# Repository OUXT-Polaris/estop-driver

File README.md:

# estop-driver
PCB design files for a board that brings an emergency stop function with mechanical relays to the power supply of an autonomous mobile robot.

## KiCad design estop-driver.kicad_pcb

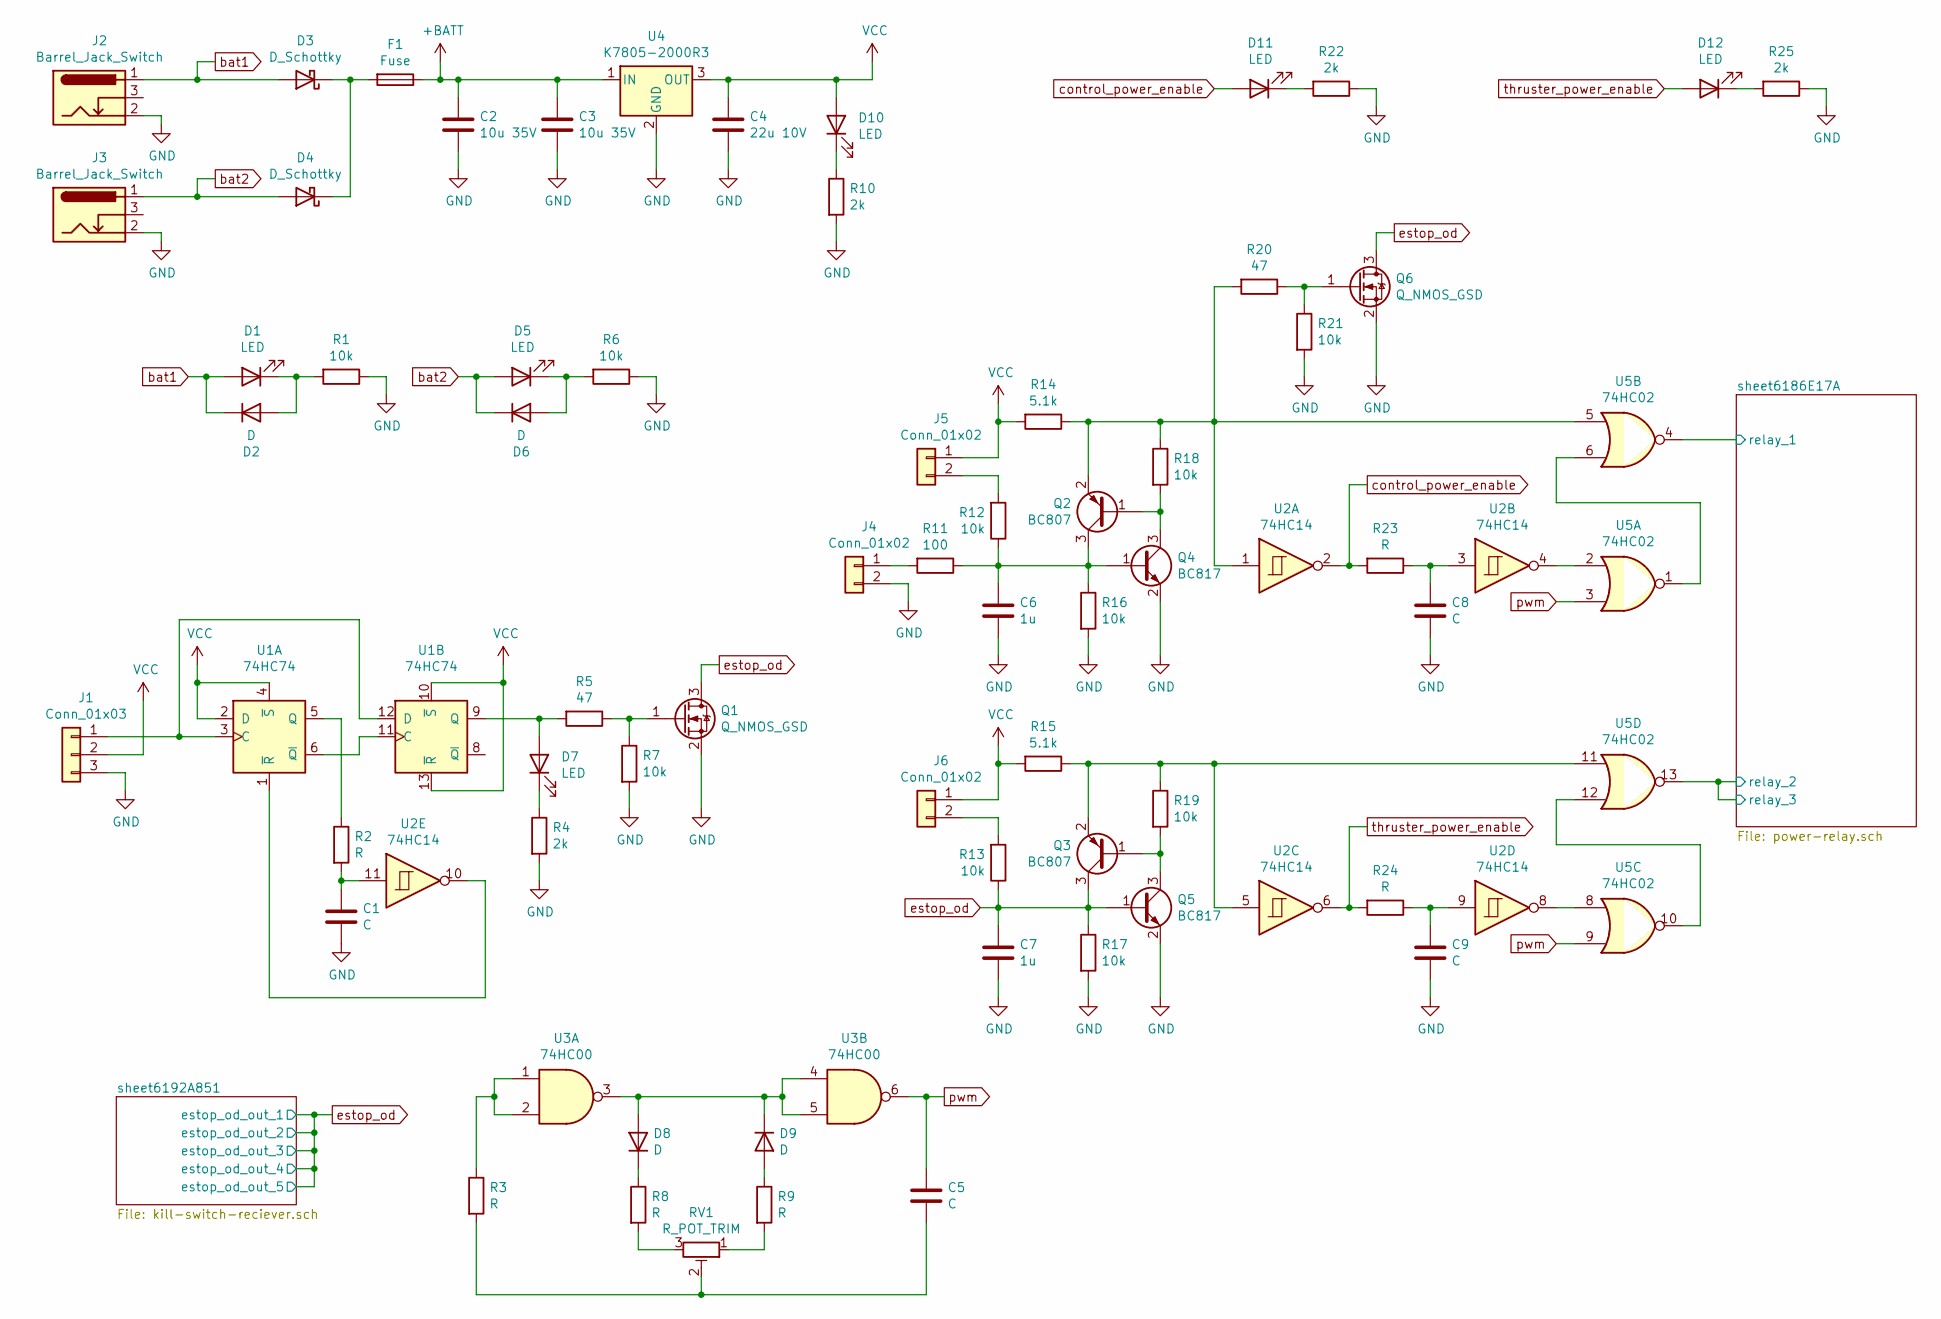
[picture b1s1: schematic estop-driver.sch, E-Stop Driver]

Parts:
C1, C5, C8, C9: C; C_0805_2012Metric_Pad1.15x1.40mm_HandSolder
C2, C3: 10u 35V; C_0805_2012Metric_Pad1.15x1.40mm_HandSolder
C4: 22u 10V; C_1206_3216Metric_Pad1.33x1.80mm_HandSolder
C6, C7: 1u; C_0805_2012Metric_Pad1.15x1.40mm_HandSolder
D1, D5, D7, D10, D11, D12: LED; LED_0603_1608Metric_Pad1.05x0.95mm_HandSolder
D2, D6, D8, D9: D; D_SOD-123
D3, D4: D_Schottky; D_SMC
F1: Fuse; RSPRO_1884617_plus_fuse
J1: Conn_01x03; PinHeader_1x03_P2.54mm_Vertical
J2, J3: Barrel_Jack_Switch; BarrelJack_Horizontal
J4, J5, J6: Conn_01x02; PinHeader_1x02_P2.54mm_Vertical
Q1, Q6: Q_NMOS_GSD; SOT-323_SC-70
Q2, Q3: BC807; SOT-23
Q4, Q5: BC817; SOT-23
R1, R6, R7, R12, R13, R16, R17, R18, R19, R21: 10k; R_0603_1608Metric_Pad0.98x0.95mm_HandSolder
R2, R3, R8, R9, R23, R24: R; R_0603_1608Metric_Pad0.98x0.95mm_HandSolder
R4, R10, R22, R25: 2k; R_0603_1608Metric_Pad0.98x0.95mm_HandSolder
R5, R20: 47; R_0603_1608Metric_Pad0.98x0.95mm_HandSolder
R11: 100; R_0603_1608Metric_Pad0.98x0.95mm_HandSolder
R14, R15: 5.1k; R_0603_1608Metric_Pad0.98x0.95mm_HandSolder
RV1: R_POT_TRIM; Potentiometer_Bourns_3296Y_Vertical
U1: 74HC74; SOIC-14_3.9x8.7mm_P1.27mm
U2: 74HC14; SOIC-14_3.9x8.7mm_P1.27mm
U3: 74HC00; SOIC-14_3.9x8.7mm_P1.27mm
U4: K7805-2000R3; RSPRO_K78xx-2000R3
U5: 74HC02; SOIC-14_3.9x8.7mm_P1.27mm

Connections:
+BATT: C2.1, C3.1, F1.1, U4.1 (IN); also elsewhere on the board
/sheet6186E17A/relay_1: U5.4; also elsewhere on the board
/sheet6186E17A/relay_2: U5.13; also elsewhere on the board
GND: C1.2, C2.2, C3.2, C4.2, C6.2, C7.2, C8.2, C9.2, J1.3, J2.2, J3.2, J4.2, Q1.2 (S), Q4.2 (E), Q5.2 (E), Q6.2 (S), R1.1, R4.2, R6.1, R7.2, R10.2, R16.2, R17.2, R21.2, R22.1, R25.1, U4.2 (GND); also elsewhere on the board
unnamed: C1.1, R2.2, U2.11
unnamed: C5.2, R3.2, RV1.2
unnamed: C6.1, Q2.3 (C), Q4.1 (B), R11.1, R12.1, R16.1
unnamed: C8.1, R23.1, U2.3
unnamed: C9.1, R24.1, U2.9
unnamed: D1.1 (K), D2.2 (A), R1.2
unnamed: D3.1 (K), D4.1 (K), F1.2
unnamed: D5.1 (K), D6.2 (A), R6.2
unnamed: D7.1 (K), R4.1
unnamed: D7.2 (A), R5.2, U1.9 (Q)
unnamed: D8.1 (K), R8.1
unnamed: D8.2 (A), D9.1 (K), U3.3, U3.4, U3.5
unnamed: D9.2 (A), R9.1
unnamed: D10.1 (K), R10.1
unnamed: D11.1 (K), R22.2
unnamed: D12.1 (K), R25.2
unnamed: J1.1, U1.3 (C), U1.12 (D)
unnamed: J4.1, R11.2
unnamed: J5.2, R12.2
unnamed: J6.2, R13.2
unnamed: Q1.1 (G), R5.1, R7.1
unnamed: Q2.1 (B), Q4.3 (C), R18.2
unnamed: Q2.2 (E), R14.1, R18.1, R20.2, U2.1, U5.5
unnamed: Q3.1 (B), Q5.3 (C), R19.2
unnamed: Q3.2 (E), R15.1, R19.1, U2.5, U5.11
unnamed: Q6.1 (G), R20.1, R21.1
unnamed: R2.1, U1.5 (Q)
unnamed: R3.1, U3.1, U3.2
unnamed: R8.2, RV1.3
unnamed: R9.2, RV1.1
unnamed: U1.1 (~R), U2.10
unnamed: U1.6 (~Q), U1.11 (C)
unnamed: U2.4, U5.2
unnamed: U2.8, U5.8
unnamed: U5.1, U5.6
unnamed: U5.10, U5.12
VCC: C4.1, D10.2 (A), J1.2, J5.1, J6.1, R14.2, R15.2, U1.2 (D), U1.4 (~S), U1.10 (~S), U1.13 (~R), U4.3 (OUT); also elsewhere on the board
bat1: D1.2 (A), D2.1 (K), D3.2 (A), J2.1
bat2: D4.2 (A), D5.2 (A), D6.1 (K), J3.1
control_power_enable: D11.2 (A), R23.2, U2.2
estop_od: C7.1, Q1.3 (D), Q3.3 (C), Q5.1 (B), Q6.3 (D), R13.1, R17.1; also elsewhere on the board
pwm: C5.1, U3.6, U5.3, U5.9
thruster_power_enable: D12.2 (A), R24.2, U2.6

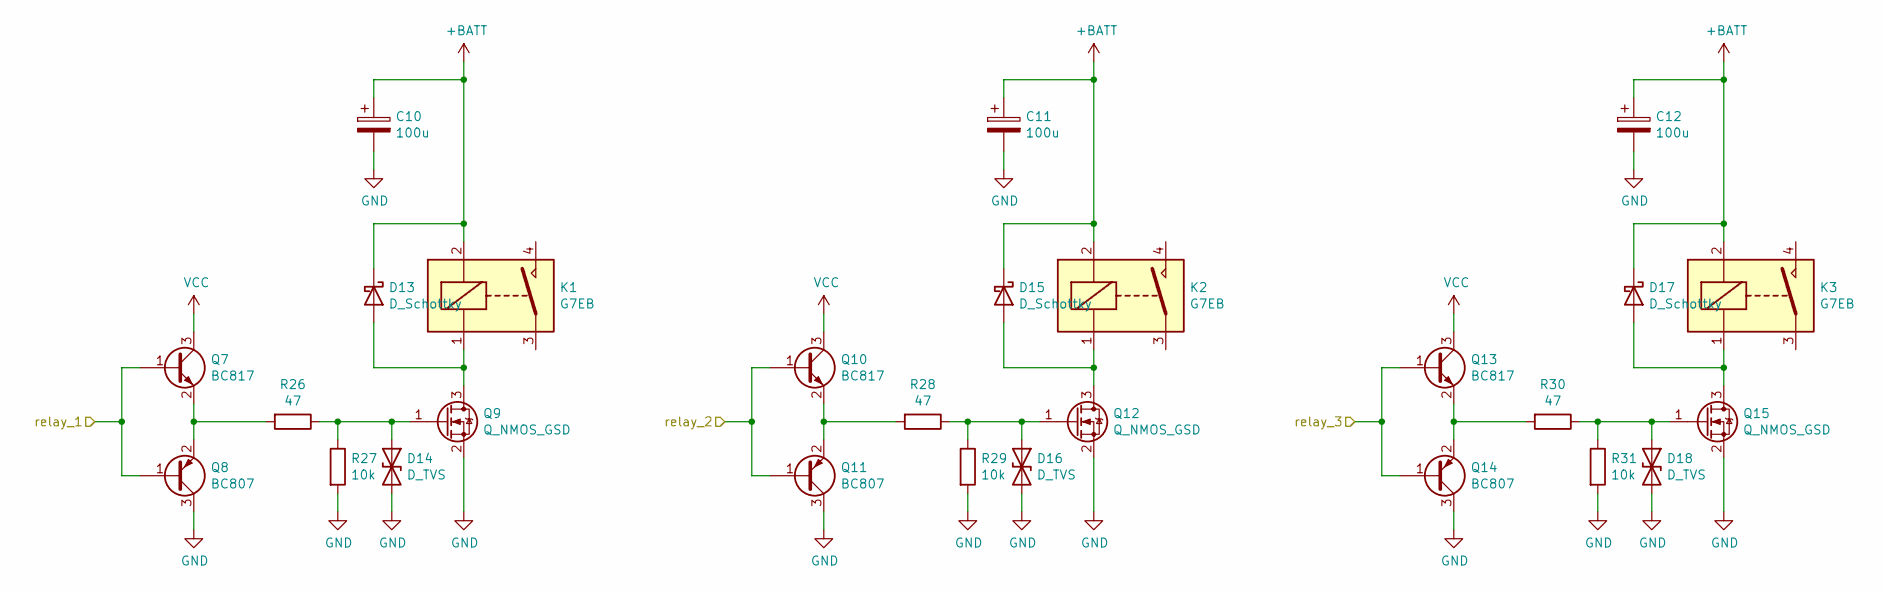
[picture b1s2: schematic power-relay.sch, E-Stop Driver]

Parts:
C10, C11, C12: 100u; C_Elec_8x5.4
D13, D15, D17: D_Schottky; D_SMA
D14, D16, D18: D_TVS; D_SMA
K1, K2, K3: G7EB; G7EB-1A
Q7, Q10, Q13: BC817; SOT-23
Q8, Q11, Q14: BC807; SOT-23
Q9, Q12, Q15: Q_NMOS_GSD; SOT-23
R26, R28, R30: 47; R_0603_1608Metric_Pad0.98x0.95mm_HandSolder
R27, R29, R31: 10k; R_0603_1608Metric_Pad0.98x0.95mm_HandSolder

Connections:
+BATT: C10.1, C11.1, C12.1, D13.1 (K), D15.1 (K), D17.1 (K), K1.2, K2.2, K3.2; also elsewhere on the board
/sheet6186E17A/relay_1: Q7.1 (B), Q8.1 (B); also elsewhere on the board
/sheet6186E17A/relay_2: Q10.1 (B), Q11.1 (B), Q13.1 (B), Q14.1 (B); also elsewhere on the board
GND: C10.2, C11.2, C12.2, D14.2 (A2), D16.2 (A2), D18.2 (A2), Q8.3 (C), Q9.2 (S), Q11.3 (C), Q12.2 (S), Q14.3 (C), Q15.2 (S), R27.2, R29.2, R31.2; also elsewhere on the board
unnamed: D13.2 (A), K1.1, Q9.3 (D)
unnamed: D14.1 (A1), Q9.1 (G), R26.1, R27.1
unnamed: D15.2 (A), K2.1, Q12.3 (D)
unnamed: D16.1 (A1), Q12.1 (G), R28.1, R29.1
unnamed: D17.2 (A), K3.1, Q15.3 (D)
unnamed: D18.1 (A1), Q15.1 (G), R30.1, R31.1
unnamed: Q7.2 (E), Q8.2 (E), R26.2
unnamed: Q10.2 (E), Q11.2 (E), R28.2
unnamed: Q13.2 (E), Q14.2 (E), R30.2
VCC: Q7.3 (C), Q10.3 (C), Q13.3 (C); also elsewhere on the board

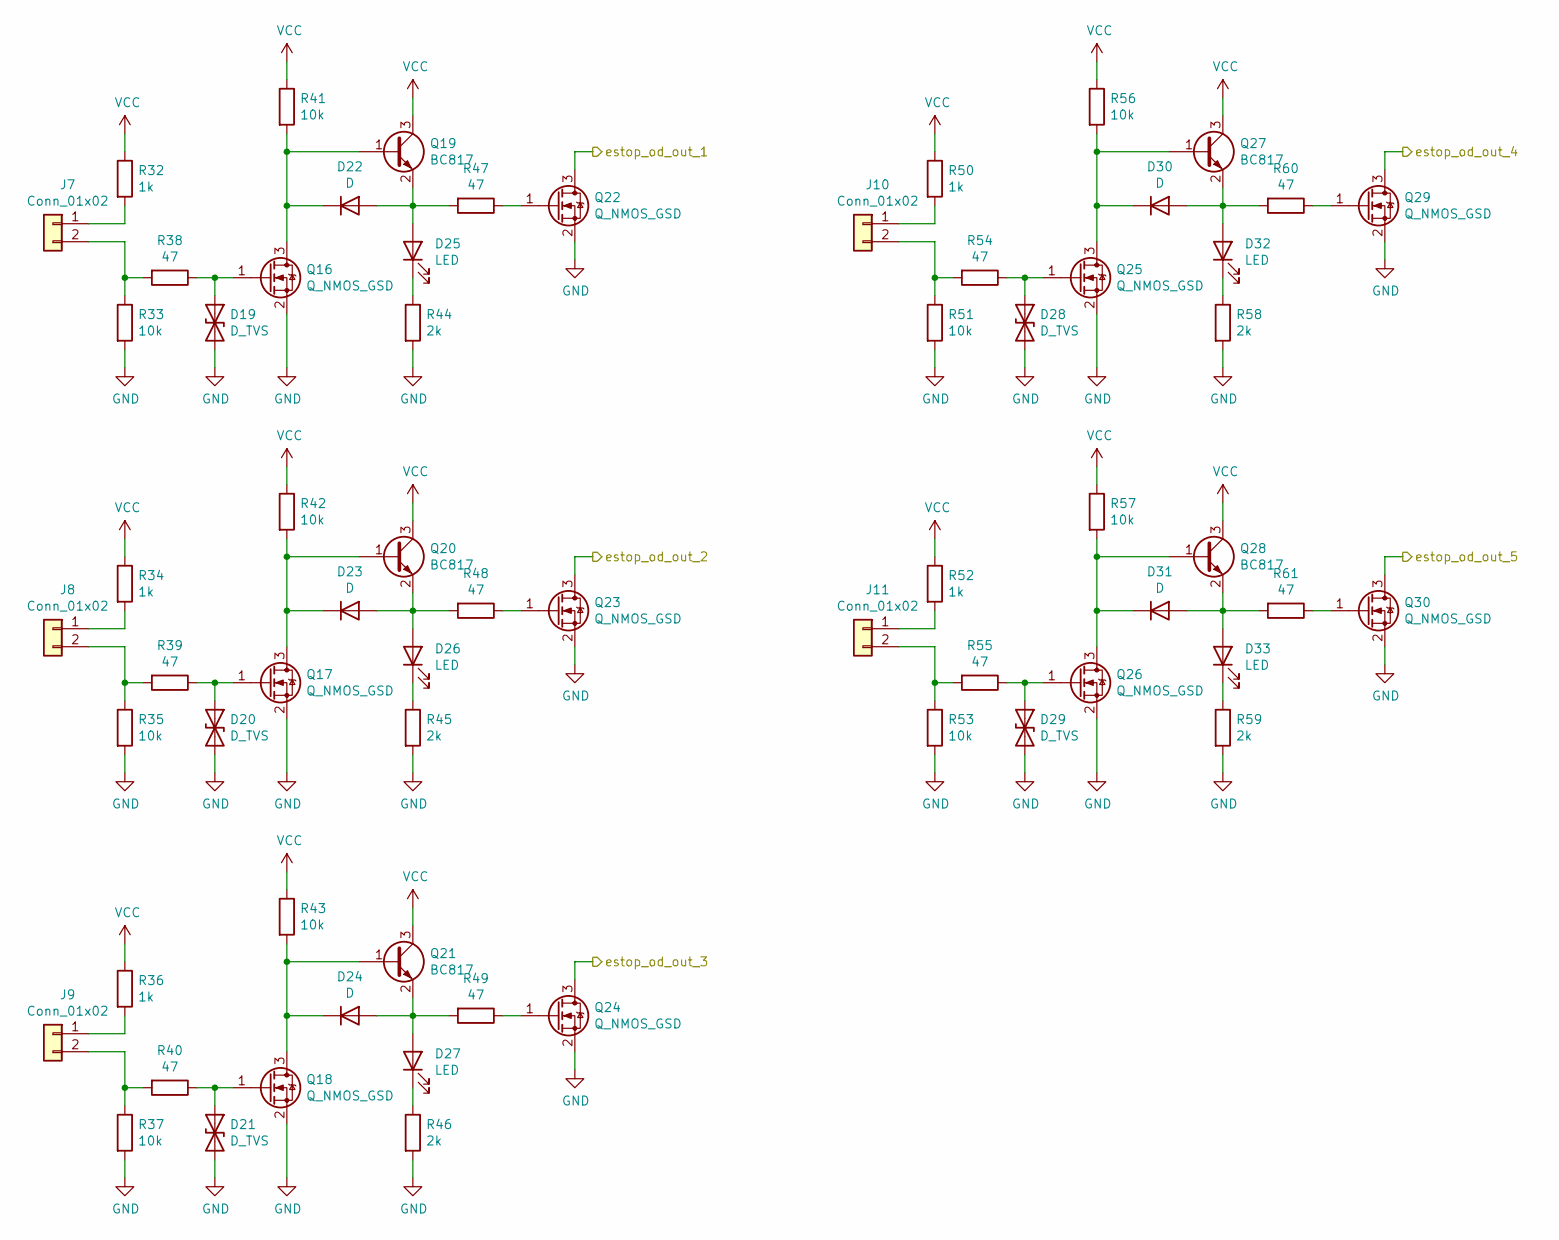
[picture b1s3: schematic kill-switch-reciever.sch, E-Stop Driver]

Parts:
D19, D20, D21, D28, D29: D_TVS; D_SMA
D22, D23, D24, D30, D31: D; D_SOD-123
D25, D26, D27, D32, D33: LED; LED_0603_1608Metric_Pad1.05x0.95mm_HandSolder
J7, J8, J9, J10, J11: Conn_01x02; PinHeader_1x02_P2.54mm_Vertical
Q16, Q17, Q18, Q22, Q23, Q24, Q25, Q26, Q29, Q30: Q_NMOS_GSD; SOT-323_SC-70
Q19, Q20, Q21, Q27, Q28: BC817; SOT-23
R32, R34, R36, R50, R52: 1k; R_0603_1608Metric_Pad0.98x0.95mm_HandSolder
R33, R35, R37, R41, R42, R43, R51, R53, R56, R57: 10k; R_0603_1608Metric_Pad0.98x0.95mm_HandSolder
R38, R39, R40, R47, R48, R49, R54, R55, R60, R61: 47; R_0603_1608Metric_Pad0.98x0.95mm_HandSolder
R44, R45, R46, R58, R59: 2k; R_0603_1608Metric_Pad0.98x0.95mm_HandSolder

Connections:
GND: D19.2 (A2), D20.2 (A2), D21.2 (A2), D28.2 (A2), D29.2 (A2), Q16.2 (S), Q17.2 (S), Q18.2 (S), Q22.2 (S), Q23.2 (S), Q24.2 (S), Q25.2 (S), Q26.2 (S), Q29.2 (S), Q30.2 (S), R33.2, R35.2, R37.2, R44.2, R45.2, R46.2, R51.2, R53.2, R58.2, R59.2; also elsewhere on the board
unnamed: D19.1 (A1), Q16.1 (G), R38.1
unnamed: D20.1 (A1), Q17.1 (G), R39.1
unnamed: D21.1 (A1), Q18.1 (G), R40.1
unnamed: D22.1 (K), Q16.3 (D), Q19.1 (B), R41.2
unnamed: D22.2 (A), D25.2 (A), Q19.2 (E), R47.2
unnamed: D23.1 (K), Q17.3 (D), Q20.1 (B), R42.2
unnamed: D23.2 (A), D26.2 (A), Q20.2 (E), R48.2
unnamed: D24.1 (K), Q18.3 (D), Q21.1 (B), R43.2
unnamed: D24.2 (A), D27.2 (A), Q21.2 (E), R49.2
unnamed: D25.1 (K), R44.1
unnamed: D26.1 (K), R45.1
unnamed: D27.1 (K), R46.1
unnamed: D28.1 (A1), Q25.1 (G), R54.1
unnamed: D29.1 (A1), Q26.1 (G), R55.1
unnamed: D30.1 (K), Q25.3 (D), Q27.1 (B), R56.2
unnamed: D30.2 (A), D32.2 (A), Q27.2 (E), R60.2
unnamed: D31.1 (K), Q26.3 (D), Q28.1 (B), R57.2
unnamed: D31.2 (A), D33.2 (A), Q28.2 (E), R61.2
unnamed: D32.1 (K), R58.1
unnamed: D33.1 (K), R59.1
unnamed: J7.1, R32.2
unnamed: J7.2, R33.1, R38.2
unnamed: J8.1, R34.2
unnamed: J8.2, R35.1, R39.2
unnamed: J9.1, R36.2
unnamed: J9.2, R37.1, R40.2
unnamed: J10.1, R50.2
unnamed: J10.2, R51.1, R54.2
unnamed: J11.1, R52.2
unnamed: J11.2, R53.1, R55.2
unnamed: Q22.1 (G), R47.1
unnamed: Q23.1 (G), R48.1
unnamed: Q24.1 (G), R49.1
unnamed: Q29.1 (G), R60.1
unnamed: Q30.1 (G), R61.1
VCC: Q19.3 (C), Q20.3 (C), Q21.3 (C), Q27.3 (C), Q28.3 (C), R32.1, R34.1, R36.1, R41.1, R42.1, R43.1, R50.1, R52.1, R56.1, R57.1; also elsewhere on the board
estop_od: Q22.3 (D), Q23.3 (D), Q24.3 (D), Q29.3 (D), Q30.3 (D); also elsewhere on the board

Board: 2 copper layers, 157 parts (0 on the bottom side), 91 nets, no tracks yet.

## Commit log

2021-08-17 Add KiCad files
2021-08-25 Update KiCad files
2021-08-25 Add schematics images for readme
2021-08-26 set example workflow
2021-08-26 enable dispatch manually
